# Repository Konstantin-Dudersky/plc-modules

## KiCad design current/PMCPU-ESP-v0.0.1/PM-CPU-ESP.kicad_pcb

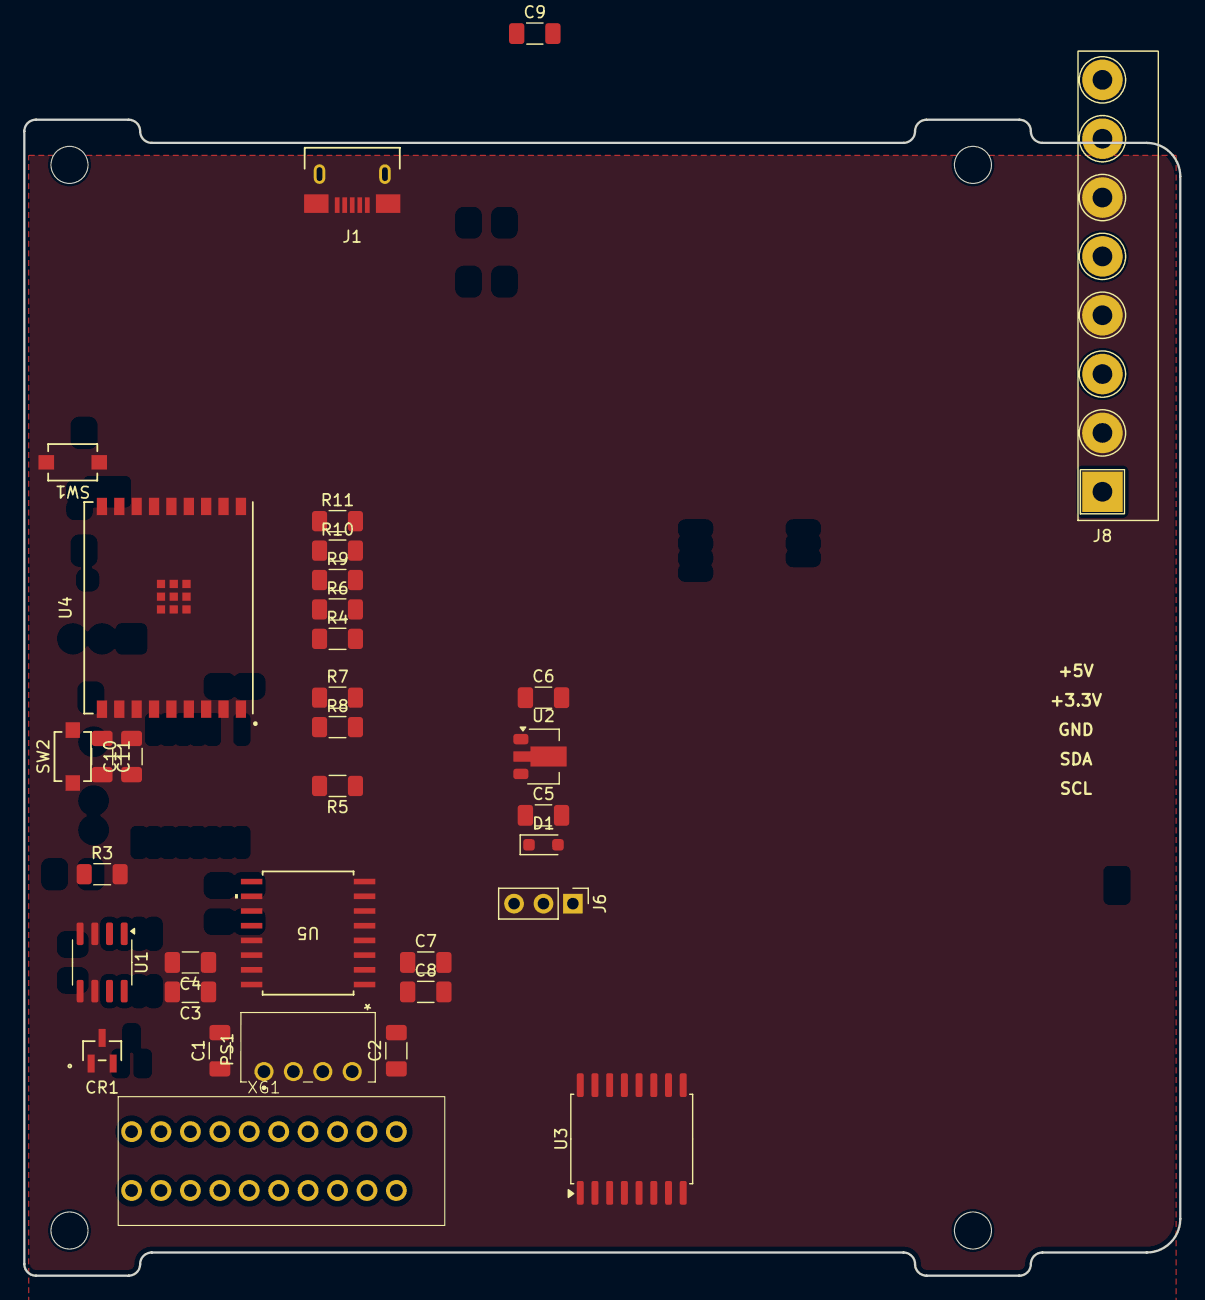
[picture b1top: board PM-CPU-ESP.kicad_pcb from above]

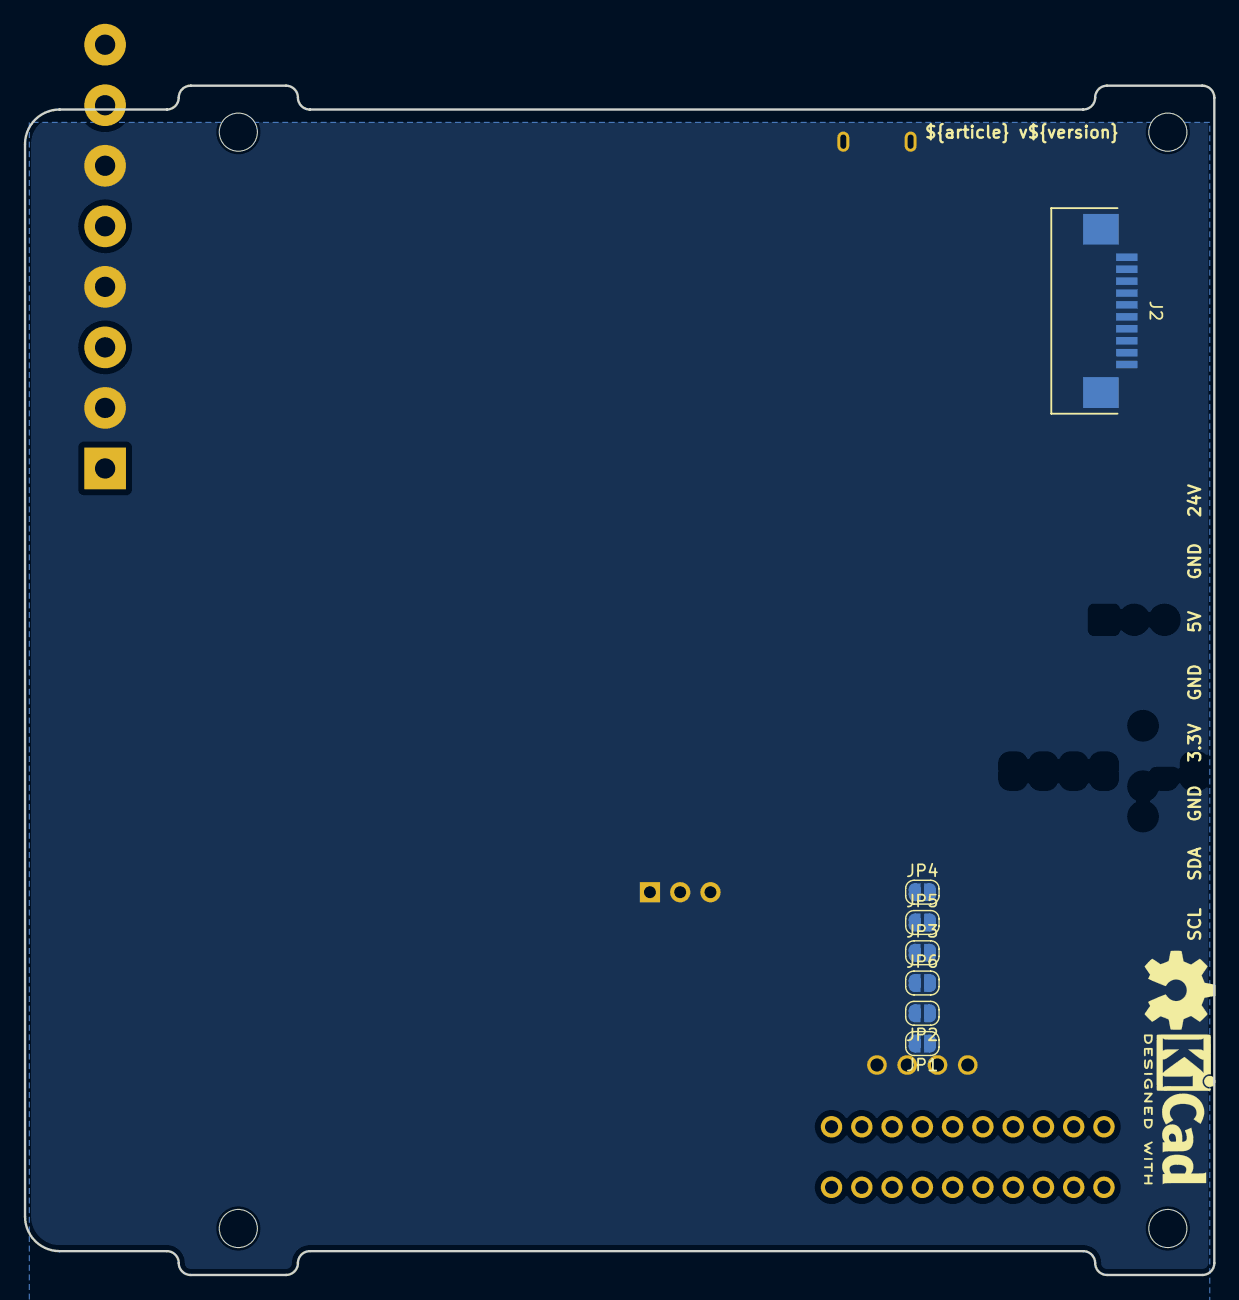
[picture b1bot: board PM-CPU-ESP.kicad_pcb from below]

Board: 2 copper layers, 99.8 x 99.8 mm, 47 parts (9 on the bottom side), 30 nets, no tracks yet.

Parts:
C1, C2, C3, C5, C7, C10: 10uF; C_1206_3216Metric_Pad1.33x1.80mm_HandSolder
C4, C8: 100nF; C_1206_3216Metric_Pad1.33x1.80mm_HandSolder
C6: 22uF; C_1206_3216Metric_Pad1.33x1.80mm_HandSolder
C9, C11: 1uF; C_1206_3216Metric_Pad1.33x1.80mm_HandSolder
CR1: SM712; SOT23-3_LTF-M
D1: 5A 9.8V 6V; D_SOD-323_HandSoldering
H1, H2, H3, H4: MountingHole; MountingHole_3.2mm_M3
J1: U254-051T-4BH83-S1S; CONN5_H83-S1S_XKB
J2: AFA07-S10FCC-00; CONN10_AFA07-S10_JUS
J6: PinHeader_01x03_P2.54_THT_straight; PinHeader_1x03_P2.54mm_Vertical
J8: 2EDGR-5.08-08P; Degson_2EDGR-5.08-08P
JP1, JP2, JP3, JP4, JP5, JP6: SolderJumper_2_Open; SolderJumper-2_P1.3mm_Open_RoundedPad1.0x1.5mm
PS1: B0505S-1WR3; B0505S1WR3
R3, R4, R6, R9, R10, R11: 10k; R_1206_3216Metric_Pad1.30x1.75mm_HandSolder
R5: 330R; R_1206_3216Metric_Pad1.30x1.75mm_HandSolder
R7, R8: 3k3; R_1206_3216Metric_Pad1.30x1.75mm_HandSolder
SW1, SW2: Button; SW_TS-1088_XNP-M
U1: MAX3485; SOIC-8_3.9x4.9mm_P1.27mm
U2: CJA1117B-3.3; SOT-89-3
U3: DS3231; SOIC-16W_7.5x10.3mm_P1.27mm
U4: ESP32-C3-WROOM-02U-N4; ESP32-C3-WROOM-02U_EXP
U5: CA-IS3641HW; SOIC16-WBW_CLG-M
XG1: DG141R-2.54-10P
kicad_logo: KiCad-Logo2_5mm_SilkScreen
oshw_logo: OSHW-Symbol_6.7x6mm_SilkScreen

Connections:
+3.3V: C6.1, C7.1, C8.1, C10.2, C11.1, J2.2, J8.5, JP6.1 (A), R4.1, R6.1, R7.1, R8.1, R9.1, R10.1, R11.1, U2.2 (OUTPUT), U4.1 (3V3), U5.1 (VDD)
+3.3V_ISO: C3.1, C4.1, JP6.2 (B), U1.8 (VCC), U5.16 (VISO)
+5V: C5.1, D1.1 (A1), J2.1, J6.2, J8.3, U2.3 (INPUT), U3.2 (VCC)
+5V_ISO: C1.1, JP1.1 (A), PS1.1 (GND), XG1.1, XG1.6
/A: CR1.1, U1.6 (A), XG1.3, XG1.8
/B: CR1.2, U1.7 (B), XG1.4, XG1.9
/CS0: J2.6, R11.2, U4.10 (IO10)
/CS1: J2.7, R10.2, U4.16 (IO2)
/CS2: J2.8, R6.2, U4.7 (IO8)
/CS3: J2.9, R4.2, R5.1, U4.8 (IO9)
/EN: C9.1, R9.2, SW2.2, U4.2 (EN)
/MISO: J2.4, U4.17 (IO1)
/MOSI: J2.3, U4.18 (IO0)
/SCK: J2.5, U4.15 (IO3)
/SCL: J8.8, R8.2, U3.15 (SDA), U4.4 (IO5)
/SDA: J8.7, R7.2, U3.16 (SCL), U4.5 (IO6)
/UART_RTS: JP5.1 (A), U4.3 (IO4), U5.4 (VI2)
/UART_RTS_ISO: JP5.2 (B), R3.1, U1.2 (~RE), U1.3 (DE), U5.13 (VO2)
/UART_RX: JP4.1 (A), U4.11 (RXD_(IO20)), U5.6 (VO4)
/UART_RX_ISO: JP4.2 (B), U1.1 (RO), U5.11 (VI4)
/UART_TX: JP3.1 (A), U4.12 (TXD_(IO21)), U5.3 (VI1)
/UART_TX_ISO: JP3.2 (B), U1.4 (DI), U5.14 (VO1)
/USB_D+: J1.3 (D+), U4.14 (IO19_(USB_D+))
/USB_D-: J1.2 (D-), U4.13 (IO18_(USB_D-))
GND: C2.2, C5.2, C6.2, C7.2, C8.2, C9.2, C10.1, C11.2, D1.2 (A2), J1.5 (GND), J2.10, J2.11, J8.2, J8.4, J8.6, JP2.2 (B), PS1.3 (0V), SW1.1, SW2.1, U2.1 (GND), U3.5 (GND), U3.6 (GND), U3.7 (GND), U3.8 (GND), U3.9 (GND), U3.10 (GND), U3.11 (GND), U3.12 (GND), U3.13 (GND), U4.9 (GND), U4.EPAD, U5.2 (GNDA), U5.8 (GNDA)
GND_ISO: C1.2, C3.2, C4.2, CR1.3, JP2.1 (A), PS1.2 (VIN), R3.2, U1.5 (GND), U5.9 (GNDB), U5.10 (SEL), U5.15 (GNDB), XG1.2, XG1.7
unnamed: J1.1 (VBUS), J6.1
unnamed: C2.1, J6.3, JP1.2 (B), PS1.4 (+VO)
unnamed: R5.2, SW1.2
PE: XG1.5, XG1.10

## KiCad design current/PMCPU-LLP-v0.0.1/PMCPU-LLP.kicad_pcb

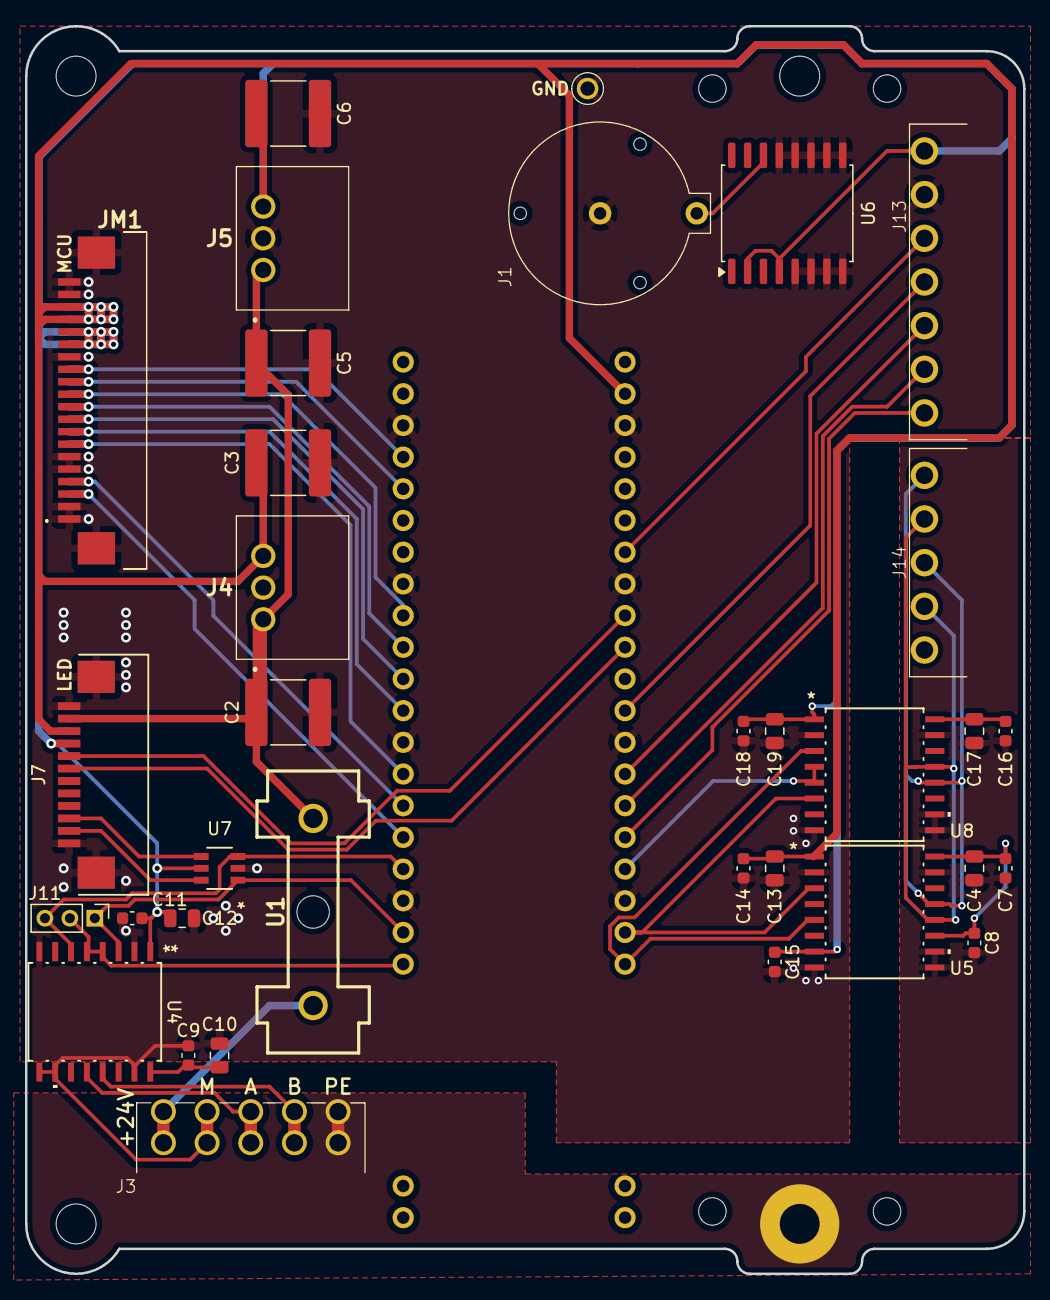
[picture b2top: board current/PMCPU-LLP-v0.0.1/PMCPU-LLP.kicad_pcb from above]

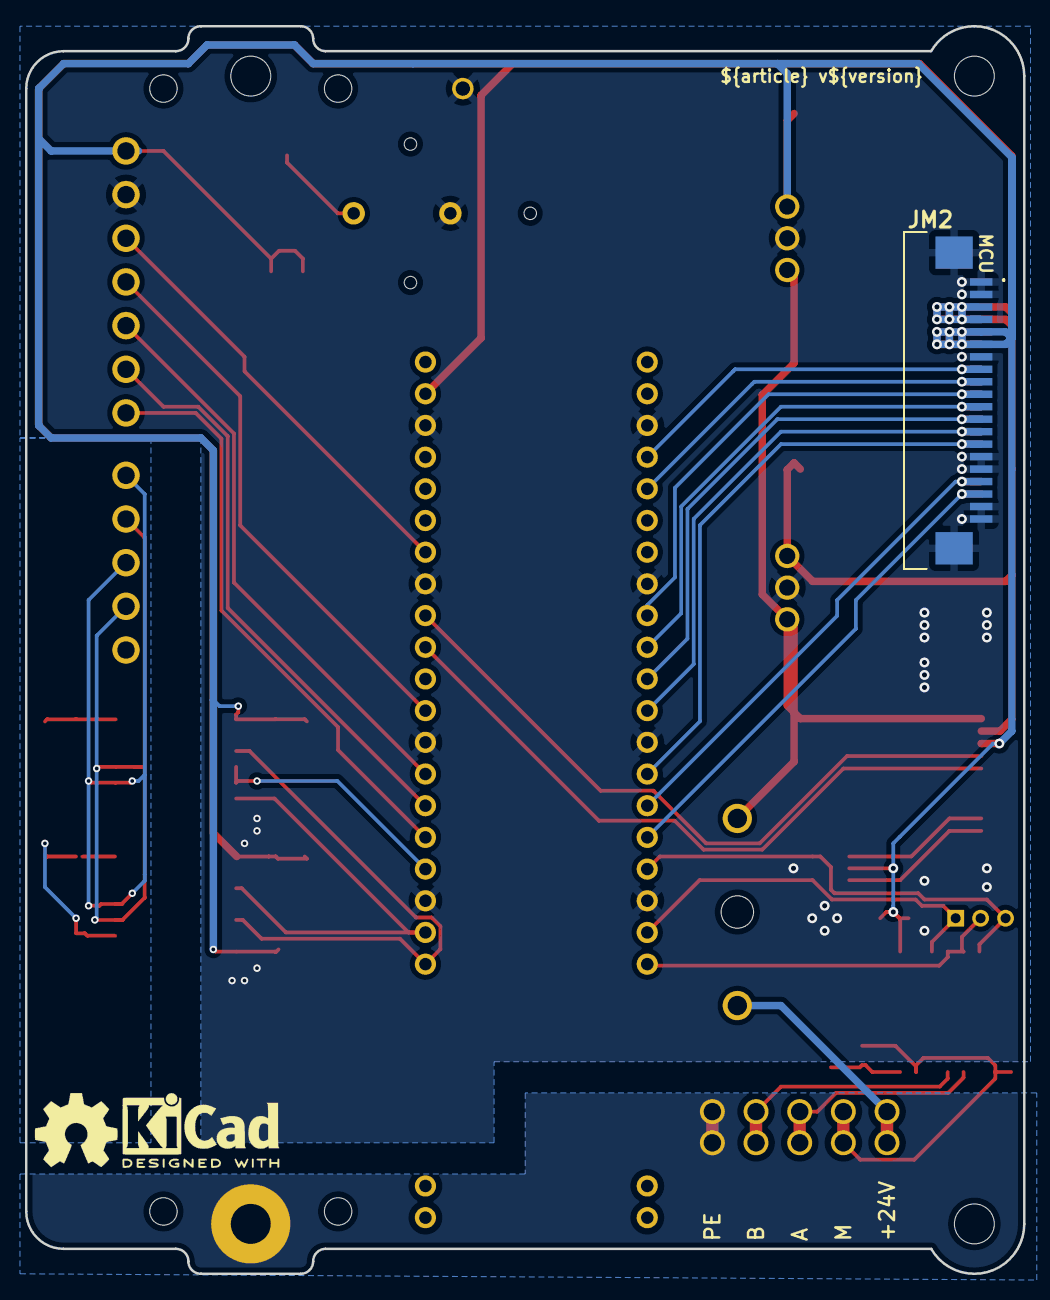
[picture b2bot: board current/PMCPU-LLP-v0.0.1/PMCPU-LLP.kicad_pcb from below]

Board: 2 copper layers, 80.0 x 100.0 mm, 43 parts (3 on the bottom side), 39 nets.

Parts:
C2, C3, C5, C6: 22uF; C_2220_5750Metric
C4, C10, C12, C13, C17, C19: 10uF; C_0805_2012Metric
C7, C9, C11, C14, C16, C18: 100nF; C_0603_1608Metric
C8, C15: 1uF; C_0603_1608Metric
H1, H2, H3: MountingHole_M3
J1: BS-12-A1AJ002-F
J3: 15EDGRHC-THR-3.5-10P
J4: K7805-2000R3
J5: K7803-2000R3; K7805-2000R3
J7: AFA07-S10FCC-00; CONN10_AFA07-S12_JUS
J11: PinHeader_01x03_P2.00_THT_straight; PinHeader_1x03_P2.00mm_Vertical
J13: 15EDGRC-3.5-07P
J14: 15EDGRC-3.5-05P
JM1, JM2: AFA07-S20FCC-00; AFA07S20FCA00
PE1: PE
SP1: PM_LED-xx-v0.0.1
U1: 64900001039; 649-Series-Holder
U2: 5117
U3: LuckfoxLyraPlus
U4, U8: CA-IS3098W; SOIC16-WBW_CLG
U5: CA-IS3062VW; SOIC16-WBW_CLG
U6: DS3231; SOIC-16W_7.5x10.3mm_P1.27mm
U7: SN74LVC2G14DBVR; DBV6-M
kicad_logo: KiCad-Logo2_5mm_SilkScreen
oshw_logo: OSHW-Symbol_6.7x6mm_SilkScreen

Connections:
+3.3V_BUS: C9.1, C10.1, U4.16 (VISO)
+3.3V_CPU: C6.1, C11.1, C12.1, C15.1, C18.1, C19.1, J5.3 (+VO), J7.9, J13.7, JM1.15 (Pin_11), JM1.16 (Pin_11), JM2.5, JM2.6, U4.1 (VDD), U5.7 (Vccl), U6.2 (VCC), U6.4 (~RST), U7.5 (VCC), U8.1 (VDD)
+3.3V_EXT: C16.1, C17.1, U8.16 (VISO)
+5V_CPU: C3.1, C13.1, C14.1, J4.3 (+VO), J7.10, JM1.17 (Pin_11), JM1.18 (Pin_11), JM2.3, JM2.4, U3.39 (VSYS), U5.1 (Vcc)
+5V_EXT: C4.1, C7.1, C8.1, U5.11 (Visoin), U5.16 (Viso)
+24V_BUS: J3.1, J3.6 (Pin_2), U1.1
+24V_fuse: C2.1, C5.1, J4.1 (VIN), J5.1 (VIN), J7.11, U1.2
/A: J3.3, J3.8 (Pin_6), U4.12 (A)
/B: J3.4, J3.9 (Pin_8), U4.13 (B)
/Ext_1: J14.3, J14.5, U5.13 (CANH), U8.12 (A)
/Ext_2: J14.2, J14.4, U5.12 (CANL), U8.13 (B)
/HMI_CLK: J13.4, U3.29 (RM_IO25)
/HMI_CS: J13.3, U3.27 (RM_IO26)
/HMI_DC: J13.2, U3.26 (RM_IO27)
/HMI_DIN: J13.5, U3.34 (RM_IO24)
/HMI_RES: J13.1, U3.25 (RM_IO28)
/I2C0_SCL: JM1.3, JM2.18 (Pin_11), U3.16 (RM_IO5)
/I2C0_SDA: JM1.4, JM2.17 (Pin_11), U3.15 (RM_IO6)
/LED_0: J7.8, U3.32 (ADC3)
/LED_1: J7.7, U3.31 (ADC2)
/RTS_EXT: U3.24 (RM_IO29), U8.4 (RE), U8.5 (DE)
/RX_EXT: U3.21 (RM_IO31), U5.5 (RXD), U8.3 (RO)
/SPI_CS0: JM1.10, JM2.11, U3.10 (RM_IO10)
/SPI_CS1: JM1.9, JM2.12 (Pin_11), U3.11 (RM_IO9)
/SPI_CS2: JM1.8, JM2.13 (Pin_11), U3.12 (RM_IO8)
/SPI_CS3: JM1.7, JM2.14 (Pin_11), U3.14 (RM_IO7)
/SPI_MISO: JM1.12 (Pin_11), JM2.9, U3.5 (RM_IO13)
/SPI_MOSI: JM1.13 (Pin_11), JM2.8, U3.4 (RM_IO12)
/SPI_SCK: JM1.11, JM2.10, U3.9 (RM_IO11)
/TX_EXT: U3.22 (RM_IO30), U5.3 (TXD), U8.6 (DI)
/UART_RTS: J11.2, U3.20 (RM_IO2), U4.4 (RE), U4.5 (DE)
/UART_RX: J11.1, U3.19 (RM_IO3), U4.3 (RO), U7.1 (1A)
/UART_RX_LED: J7.2, U7.6 (1Y)
/UART_TX: J11.3, U3.17 (RM_IO4), U4.6 (DI), U7.3 (2A)
/UART_TX_LED: J7.3, U7.4 (2Y)
/Vbat: J1.1, U6.14 (VBAT)
GND_BUS: C2.2, C3.2, C5.2, C6.2, C9.2, C10.2, C11.2, C12.2, C13.2, C14.2, C15.2, C18.2, C19.2, J1.2, J3.2 (Pin_3), J3.7 (Pin_4), J4.2 (GND), J5.2 (GND), J7.1, J7.12 (Pin_11), J7.13 (Pin_11), J13.6, JM1.1, JM1.2, JM1.5, JM1.6, JM1.14 (Pin_11), JM1.19 (Pin_11), JM1.20 (Pin_11), JM1.MP1 (Pin_11), JM1.MP2 (Pin_11), JM2.1, JM2.2, JM2.7, JM2.15 (Pin_11), JM2.16 (Pin_11), JM2.19 (Pin_11), JM2.20 (Pin_11), JM2.MP1 (Pin_11), JM2.MP2 (Pin_11), U2.1, U3.3 (GND), U3.8 (GND), U3.13 (GND), U3.18 (GND), U3.23 (GND), U3.28 (GND), U3.33 (GND), U3.38 (GND), U4.2 (GNDA), U4.8 (GNDA), U4.9 (GNDB), U4.10 (SEL), U4.15 (GNDB), U5.2 (GND1), U5.8 (GND1), U6.5 (GND), U6.6 (GND), U6.7 (GND), U6.8 (GND), U6.9 (GND), U6.10 (GND), U6.11 (GND), U6.12 (GND), U6.13 (GND), U7.2 (GND), U8.2 (GNDA), U8.8 (GNDA)
GND_EXT: C4.2, C7.2, C8.2, C16.2, C17.2, U5.9 (GND2), U5.10 (GND2), U5.15 (GND2), U8.9 (GNDB), U8.10 (SEL), U8.15 (GNDB)
PE: J3.5 (Pin_9), J3.10, PE1.1

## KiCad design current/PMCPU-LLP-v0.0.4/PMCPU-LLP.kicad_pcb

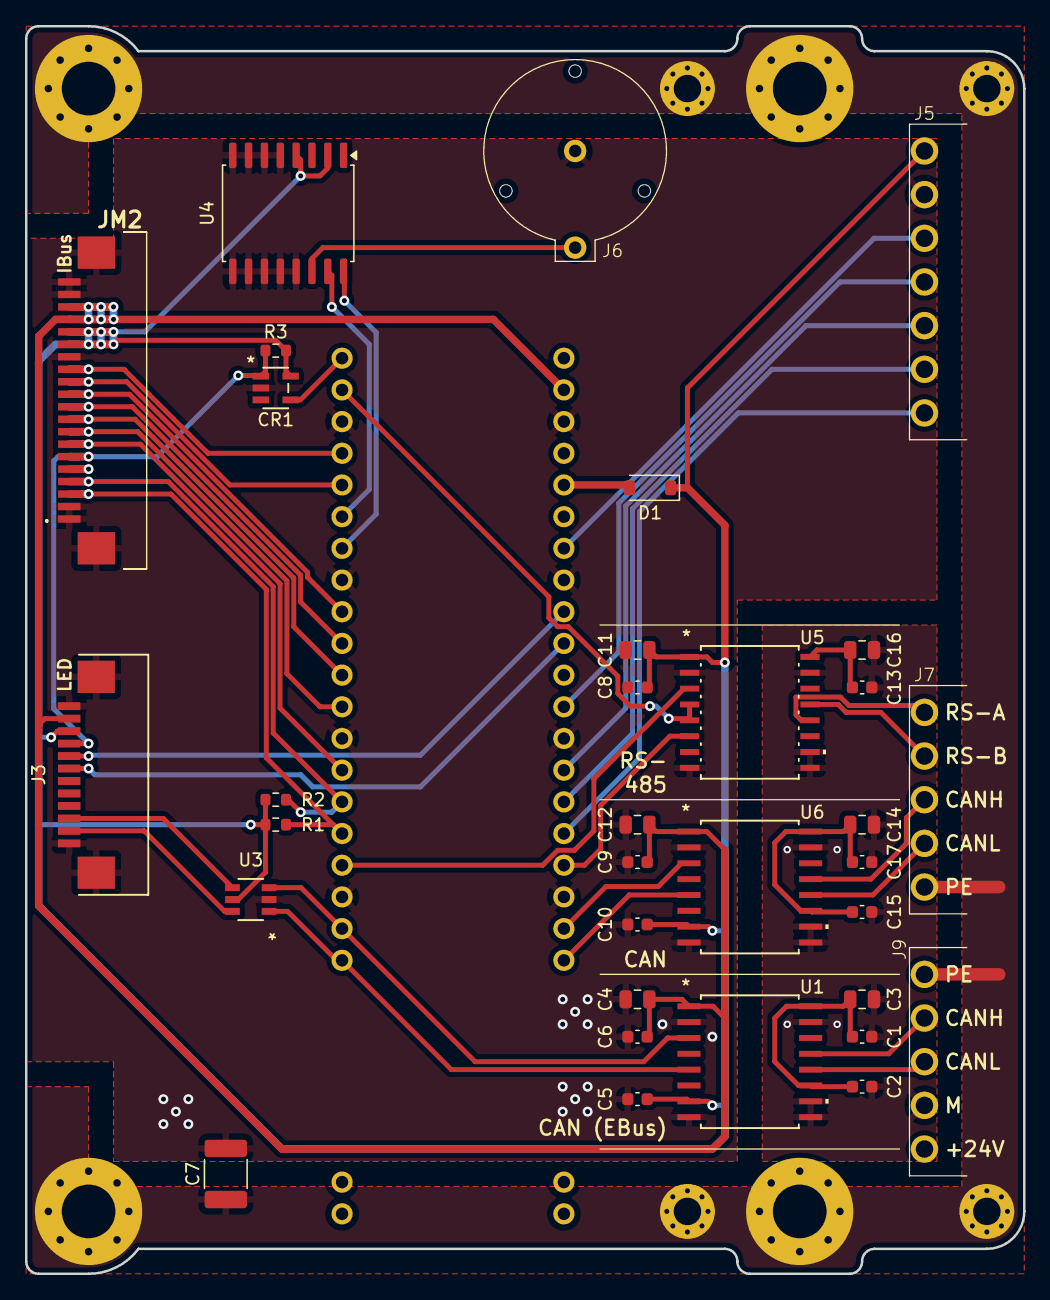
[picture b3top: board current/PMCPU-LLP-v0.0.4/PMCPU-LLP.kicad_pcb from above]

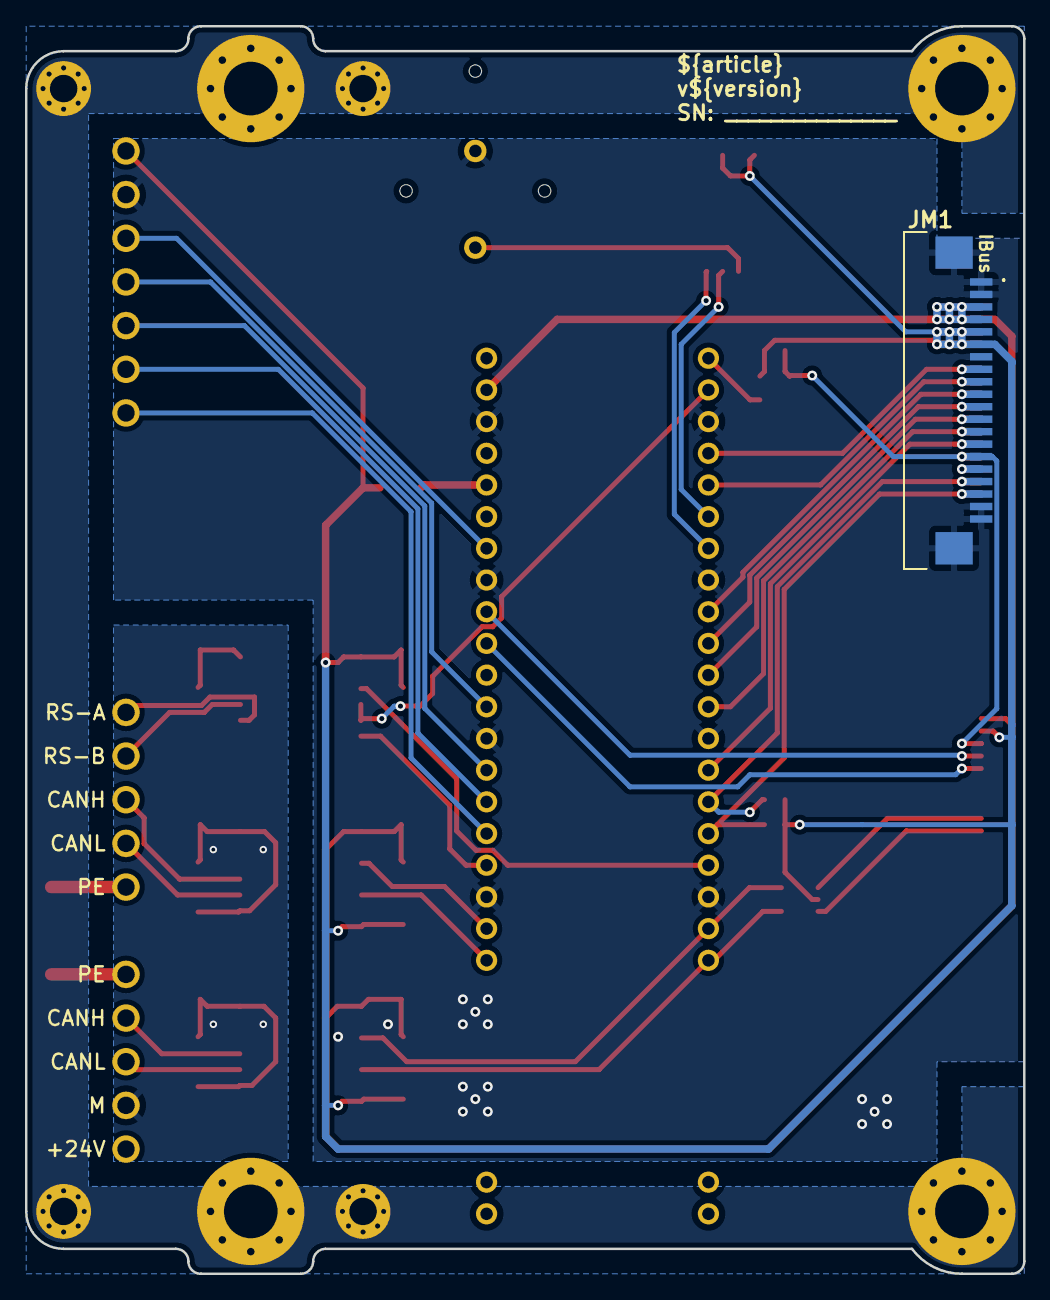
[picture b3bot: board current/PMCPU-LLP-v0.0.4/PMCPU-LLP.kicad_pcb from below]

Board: 2 copper layers, 80.0 x 100.0 mm, 42 parts (3 on the bottom side), 46 nets.

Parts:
C1, C6, C8, C9, C13, C17: 100nF; C_0603_1608Metric
C2, C5, C10, C15: 1uF; C_0603_1608Metric
C3, C4, C11, C12, C14, C16: 10uF; C_0805_2012Metric
C7: 4.7nF 2kV; C_1812_4532Metric
CR1: STWD100NYWY3F; SOT23-5L_STM
D1: B5819W; D_SOD-123
H1, H2, H3, H4: M4; MountingHole_4.3mm_M4_Pad_Via
J3: AFA07-S10FCC-00; CONN10_AFA07-S12_JUS
J5: 15EDGRC-3.5-07P
J6: BS-12-A1AJ002-F
J7, J9: 15EDGRC-3.5-05P
JM1, JM2: AFA07-S20FCC-00; AFA07S20FCA00
R1, R2: 3k3; R_0603_1608Metric
R3: 10k; R_0603_1608Metric
SP1: PMLED-xx-v0.0.2
U1, U6: CA-IS3062VW; SOIC16-WBW_CLG-M
U2: LuckfoxLyraPlus
U3: SN74LVC2G14DBVR; DBV6-M
U4: DS3231; SOIC-16W_7.5x10.3mm_P1.27mm
U5: CA-IS3098W; SOIC16-WBW_CLG
kicad_logo: KiCad-Logo2_5mm_SilkScreen
oshw_logo: OSHW-Symbol_6.7x6mm_SilkScreen

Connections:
+3.3V_CPU: C5.1, C8.1, C10.1, C11.1, CR1.5 (VCC), D1.1 (K), J3.10, J5.7, JM1.5, JM1.6, JM2.15 (Pin_11), JM2.16 (Pin_11), R1.1, R2.1, R3.1, U1.7 (Vccl), U3.5 (VCC), U4.2 (VCC), U4.4 (~RST), U5.1 (VDD), U6.7 (Vccl)
+3.3V_EXT: C13.1, C16.1, U5.16 (VISO)
+5V_BUS: C1.1, C2.1, C3.1, U1.11 (Visoin), U1.16 (Viso)
+5V_CPU: C4.1, C6.1, C9.1, C12.1, J3.11, JM1.3, JM1.4, JM2.17 (Pin_11), JM2.18 (Pin_11), U1.1 (Vcc), U2.39 (VSYS), U6.1 (Vcc)
+5V_EXT: C14.1, C15.1, C17.1, U6.11 (Visoin), U6.16 (Viso)
/CAN0_RXD: U1.5 (RXD), U2.20 (RM_IO2), U3.1 (1A)
/CAN0_RXD_LED: J3.2, U3.6 (1Y)
/CAN0_TXD: U1.3 (TXD), U2.19 (RM_IO3), U3.3 (2A)
/CAN0_TXD_LED: J3.3, U3.4 (2Y)
/CAN1_RXD: U2.21 (RM_IO31), U6.5 (RXD)
/CAN1_TXD: U2.22 (RM_IO30), U6.3 (TXD)
/CANH: J7.3, U6.13 (CANH)
/CANH_EB: J9.4, U1.13 (CANH)
/CANL: J7.2, U6.12 (CANL)
/CANL_EB: J9.3, U1.12 (CANL)
/HMI_CLK: J5.4, U2.29 (RM_IO25)
/HMI_CS: J5.3, U2.27 (RM_IO26)
/HMI_DC: J5.2, U2.26 (RM_IO27)
/HMI_DIN: J5.5, U2.34 (RM_IO24)
/HMI_RES: J5.1, U2.25 (RM_IO28)
/I2C0_SCL: JM1.18 (Pin_11), JM2.3, R1.2, U2.16 (RM_IO5)
/I2C0_SDA: JM1.17 (Pin_11), JM2.4, R2.2, U2.15 (RM_IO6)
/I2C2_SCL: U2.7 (RM_IO1), U4.16 (SCL)
/I2C2_SDA: U2.6 (RM_IO0), U4.15 (SDA)
/LED_0: J3.8, U2.32 (ADC3)
/LED_1: J3.7, U2.31 (ADC2)
/RS485-A: J7.5, U5.12 (A)
/RS485-B: J7.4, U5.13 (B)
/RST: CR1.1 (*WDO), J3.9, JM1.15 (Pin_11), JM2.6, R3.2
/SPI0_CS0: JM1.11, JM2.10, U2.10 (RM_IO10)
/SPI0_CS1: JM1.12 (Pin_11), JM2.9, U2.11 (RM_IO9)
/SPI0_CS2: JM1.13 (Pin_11), JM2.8, U2.12 (RM_IO8)
/SPI0_CS3: JM1.14 (Pin_11), JM2.7, U2.14 (RM_IO7)
/SPI0_MISO: JM1.9, JM2.12 (Pin_11), U2.5 (RM_IO13)
/SPI0_MOSI: JM1.8, JM2.13 (Pin_11), U2.4 (RM_IO12)
/SPI0_SCK: JM1.10, JM2.11, U2.9 (RM_IO11)
/UART1_RTS: U2.2 (RM_IO23), U5.4 (RE), U5.5 (DE)
/UART1_RX: U2.17 (RM_IO4), U5.3 (RO)
/UART1_TX: U2.24 (RM_IO29), U5.6 (DI)
/Vbat: J6.1, U4.14 (VBAT)
/WDT: CR1.4 (WDI), U2.1 (RM_IO22)
GND_CPU: C4.2, C5.2, C6.2, C7.2, C8.2, C9.2, C10.2, C11.2, C12.2, CR1.2 (GND), J3.1, J3.12 (Pin_11), J3.13 (Pin_11), J5.6, J6.2, JM1.1, JM1.2, JM1.7, JM1.19 (Pin_11), JM1.20 (Pin_11), JM1.MP1 (Pin_11), JM1.MP2 (Pin_11), JM2.1, JM2.2, JM2.14 (Pin_11), JM2.19 (Pin_11), JM2.20 (Pin_11), JM2.MP1 (Pin_11), JM2.MP2 (Pin_11), U1.2 (GND1), U1.8 (GND1), U2.3 (GND), U2.8 (GND), U2.13 (GND), U2.18 (GND), U2.23 (GND), U2.28 (GND), U2.33 (GND), U2.38 (GND), U3.2 (GND), U4.5 (GND), U4.6 (GND), U4.7 (GND), U4.8 (GND), U4.9 (GND), U4.10 (GND), U4.11 (GND), U4.12 (GND), U4.13 (GND), U5.2 (GNDA), U5.8 (GNDA), U6.2 (GND1), U6.8 (GND1)
GND_EB: C1.2, C2.2, C3.2, C13.2, C14.2, C15.2, C16.2, C17.2, J9.2, U1.9 (GND2), U1.10 (GND2), U1.15 (GND2), U5.9 (GNDB), U5.10 (SEL), U5.15 (GNDB), U6.9 (GND2), U6.10 (GND2), U6.15 (GND2)
unnamed: D1.2 (A), U2.36 (3V3_OUT)
unnamed: JM1.16 (Pin_11), JM2.5
PE: C7.1, H1.1, H2.1, H3.1, H4.1, J7.1, J9.5, SP1.PE

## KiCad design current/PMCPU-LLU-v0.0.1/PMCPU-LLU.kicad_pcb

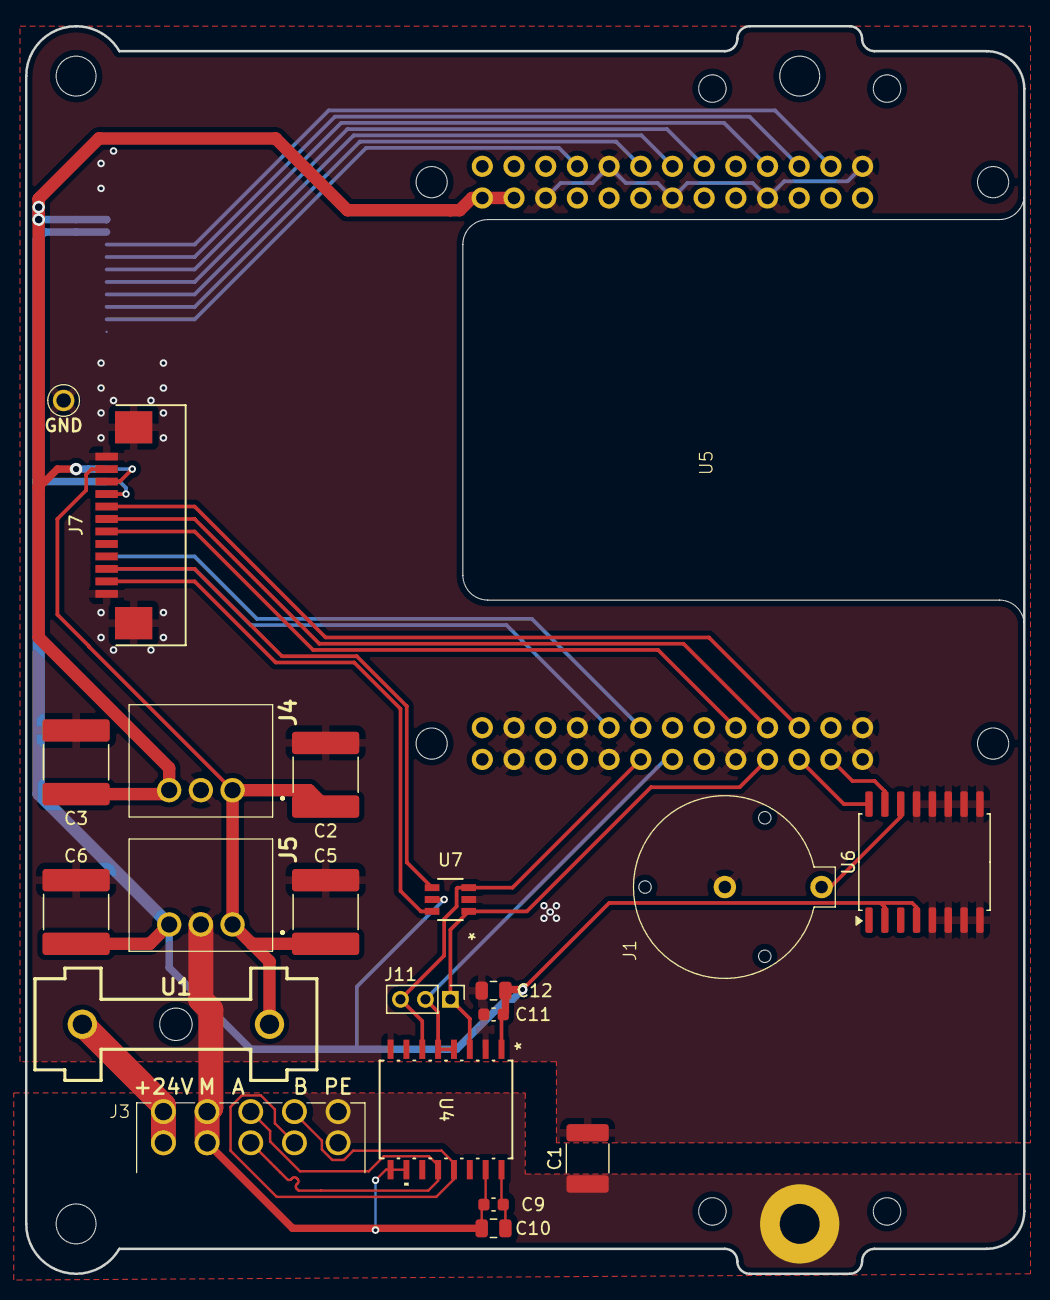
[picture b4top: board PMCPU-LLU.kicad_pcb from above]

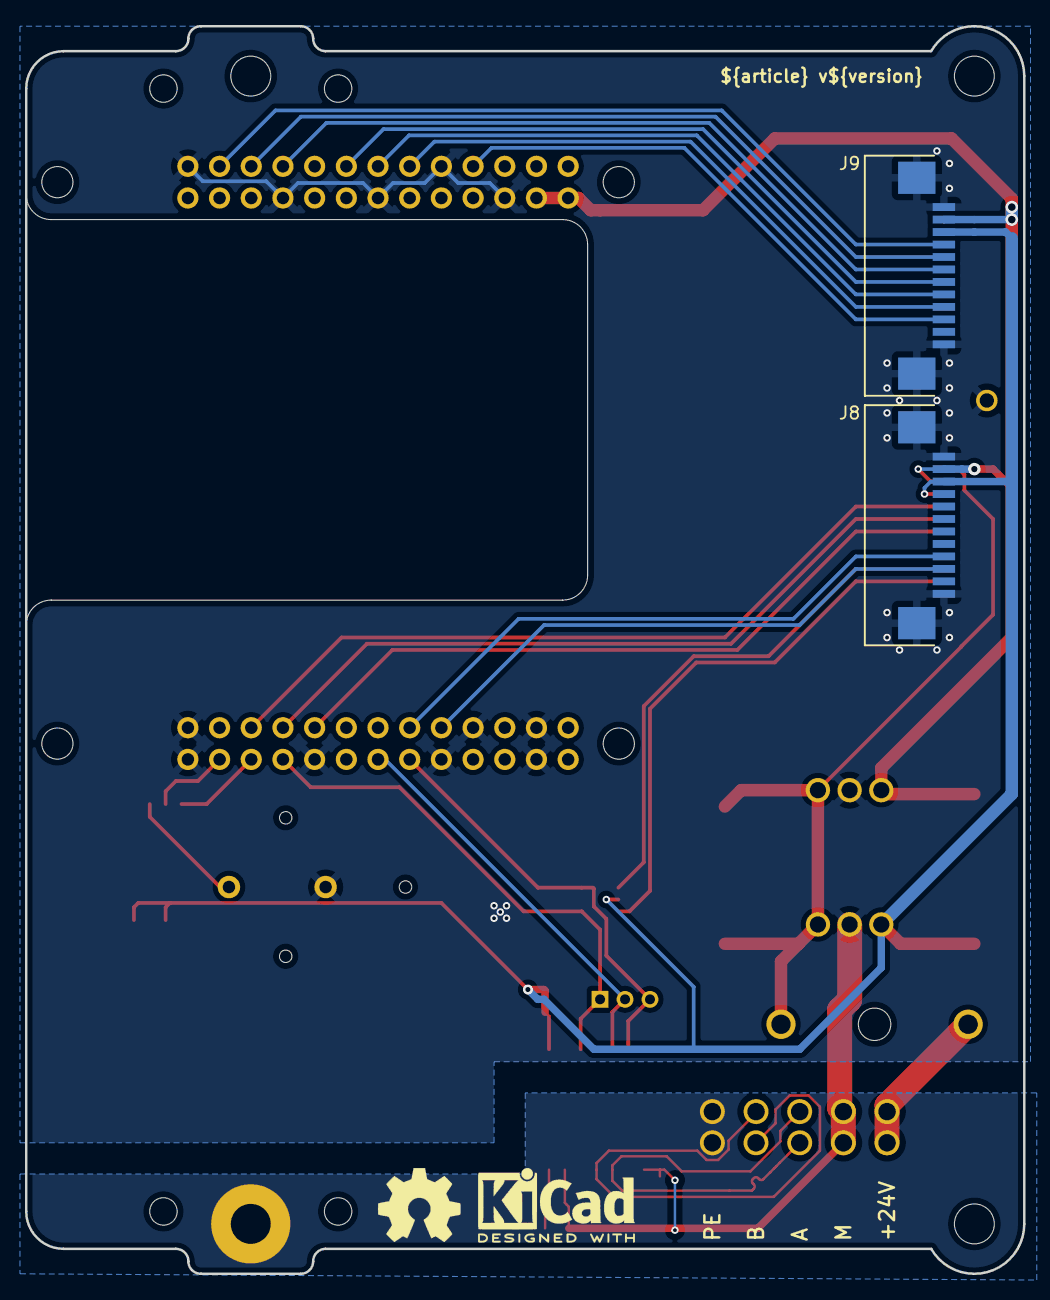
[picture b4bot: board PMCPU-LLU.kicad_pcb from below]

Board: 2 copper layers, 80.0 x 100.0 mm, 30 parts (4 on the bottom side), 29 nets.

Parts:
C1: 4.7nF 2kV; C_1812_4532Metric
C2, C3, C5, C6: 22uF; C_2220_5750Metric
C9, C11: 100nF; C_0603_1608Metric
C10, C12: 10uF; C_0805_2012Metric
H1, H2, H3: MountingHole_M3
J1: BS-12-A1AJ002-F
J3: 15EDGRHC-THR-3.5-10P
J4: K7805-2000R3
J5: K7803-2000R3; K7805-2000R3
J7, J8, J9: AFA07-S10FCC-00; CONN10_AFA07-S12_JUS
J11: PinHeader_01x03_P2.00_THT_straight; PinHeader_1x03_P2.00mm_Vertical
PE1: PE
SP1: PM_LED-xx-v0.0.1
U1: 64900001039; 649-Series-Holder
U2: 5117
U4: CA-IS3098W; SOIC16-WBW_CLG
U5: LuckfoxLyraUltra
U6: DS3231; SOIC-16W_7.5x10.3mm_P1.27mm
U7: SN74LVC2G14DBVR; DBV6-M
kicad_logo: KiCad-Logo2_5mm_SilkScreen
oshw_logo: OSHW-Symbol_6.7x6mm_SilkScreen

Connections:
+3.3V_BUS: C9.1, C10.1, U4.16 (VISO)
+3.3V_CPU: C6.1, C11.1, C12.1, J5.3 (+VO), J7.9, J8.3, J9.3, U4.1 (VDD), U6.2 (VCC), U6.4 (~RST), U7.5 (VCC)
+5V_CPU: C3.1, J4.3 (+VO), J7.10, J8.2, J9.2, U5.10 (VSYS), U5.11 (VSYS)
+24V_BUS: J3.1, J3.6 (Pin_2), U1.1
+24V_fuse: C2.1, C5.1, J4.1 (VIN), J5.1 (VIN), J7.11, U1.2
/A: J3.3, J3.8 (Pin_6), U4.12 (A)
/B: J3.4, J3.9 (Pin_8), U4.13 (B)
/I2C0_SCL: J8.10, U5.24 (RM_IO24)
/I2C0_SDA: J8.9, U5.25 (RM_IO25)
/I2C1_SCL: U5.3A (RM_IO18), U6.16 (SCL)
/I2C1_SDA: U5.3B (RM_IO20), U6.15 (SDA)
/LED_0: J7.8, U5.2A (RM_IO30)
/LED_1: J7.7, U5.29 (RM_IO29)
/LED_2: J7.6, U5.28 (RM_IO28)
/SPI_CS0: J9.7, U5.07 (RM_IO5)
/SPI_CS1: J9.8, U5.06 (RM_IO4)
/SPI_CS2: J9.9, U5.05 (RM_IO3)
/SPI_CS3: J9.10, U5.03 (RM_IO2)
/SPI_MISO: J9.5, U5.0A (RM_IO7)
/SPI_MOSI: J9.4, U5.0B (RM_IO8)
/SPI_SCK: J9.6, U5.09 (RM_IO6)
/UART_RTS: J11.2, U4.4 (RE), U4.5 (DE), U5.36
/UART_RX: J11.1, U4.3 (RO), U5.39 (RM_IO17), U7.1 (1A)
/UART_RX_LED: J7.2, U7.6 (1Y)
/UART_TX: J11.3, U4.6 (DI), U5.35 (RM_IO16), U7.3 (2A)
/UART_TX_LED: J7.3, U7.4 (2Y)
/Vbat: J1.1, U6.14 (VBAT)
GND_BUS: C1.2, C2.2, C3.2, C5.2, C6.2, C9.2, C10.2, C11.2, C12.2, J1.2, J3.2 (Pin_3), J3.7 (Pin_4), J4.2 (GND), J5.2 (GND), J7.1, J7.12 (Pin_11), J7.13 (Pin_11), J8.1, J8.12 (Pin_11), J8.13 (Pin_11), J9.1, J9.12 (Pin_11), J9.13 (Pin_11), U2.1, U4.2 (GNDA), U4.8 (GNDA), U4.9 (GNDB), U4.10 (SEL), U4.15 (GNDB), U5.0C (GND), U5.2C (GND), U5.3C (GND), U5.04 (GND), U5.12 (GND), U5.16 (GND), U5.19 (GND), U5.21 (GND), U5.23 (GND), U5.31 (GND), U5.34 (GND), U5.38 (GND), U6.5 (GND), U6.6 (GND), U6.7 (GND), U6.8 (GND), U6.9 (GND), U6.10 (GND), U6.11 (GND), U6.12 (GND), U6.13 (GND), U7.2 (GND)
PE: C1.1, J3.5 (Pin_9), J3.10, PE1.1

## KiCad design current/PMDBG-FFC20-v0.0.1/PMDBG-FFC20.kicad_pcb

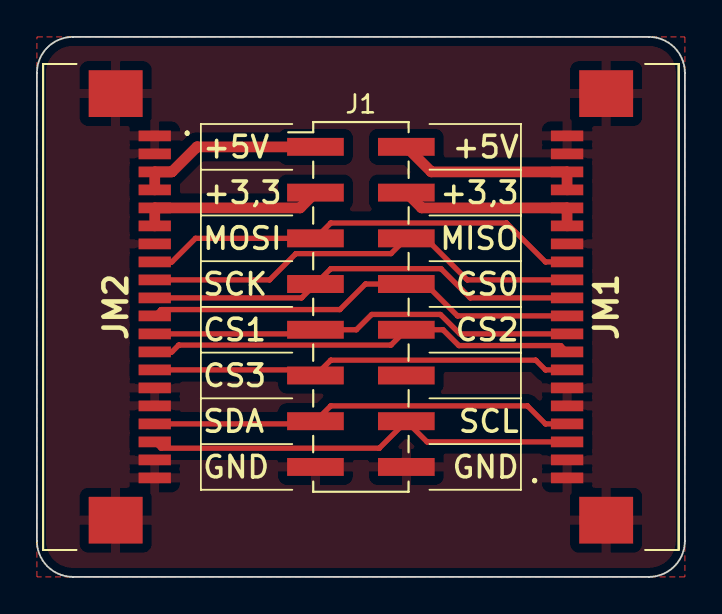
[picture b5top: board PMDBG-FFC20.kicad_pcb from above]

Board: 2 copper layers, 36.0 x 30.0 mm, 3 parts (0 on the bottom side), 14 nets.

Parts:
J1: PinHeader_02x08_P2.54_SMD_straight; PinHeader_2x08_P2.54mm_Vertical_SMD
JM1, JM2: AFA07-S20FCC-00; AFA07S20FCA00

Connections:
+3.3V_IN: J1.3, JM2.5, JM2.6
+3.3V_OUT: J1.4, JM1.15 (Pin_11), JM1.16 (Pin_11)
+5V_IN: J1.1, JM2.3, JM2.4
+5V_OUT: J1.2, JM1.17 (Pin_11), JM1.18 (Pin_11)
/CS0_MCU: J1.8, JM1.10, JM2.11
/CS1_MCU: J1.9, JM1.9, JM2.12 (Pin_11)
/CS2_MCU: J1.10, JM1.8, JM2.13 (Pin_11)
/CS3_MCU: J1.11, JM1.7, JM2.14 (Pin_11)
/MISO_MCU: J1.6, JM1.12 (Pin_11), JM2.9
/MOSI_MCU: J1.5, JM1.13 (Pin_11), JM2.8
/SCK_MCU: J1.7, JM1.11, JM2.10
/SCL_MCU: J1.14, JM1.3, JM2.18 (Pin_11)
/SDA_MCU: J1.13, JM1.4, JM2.17 (Pin_11)
GND_MCU: J1.15, J1.16, JM1.1, JM1.2, JM1.5, JM1.6, JM1.14 (Pin_11), JM1.19 (Pin_11), JM1.20 (Pin_11), JM1.MP1 (Pin_11), JM1.MP2 (Pin_11), JM2.1, JM2.2, JM2.7, JM2.15 (Pin_11), JM2.16 (Pin_11), JM2.19 (Pin_11), JM2.20 (Pin_11), JM2.MP1 (Pin_11), JM2.MP2 (Pin_11)
